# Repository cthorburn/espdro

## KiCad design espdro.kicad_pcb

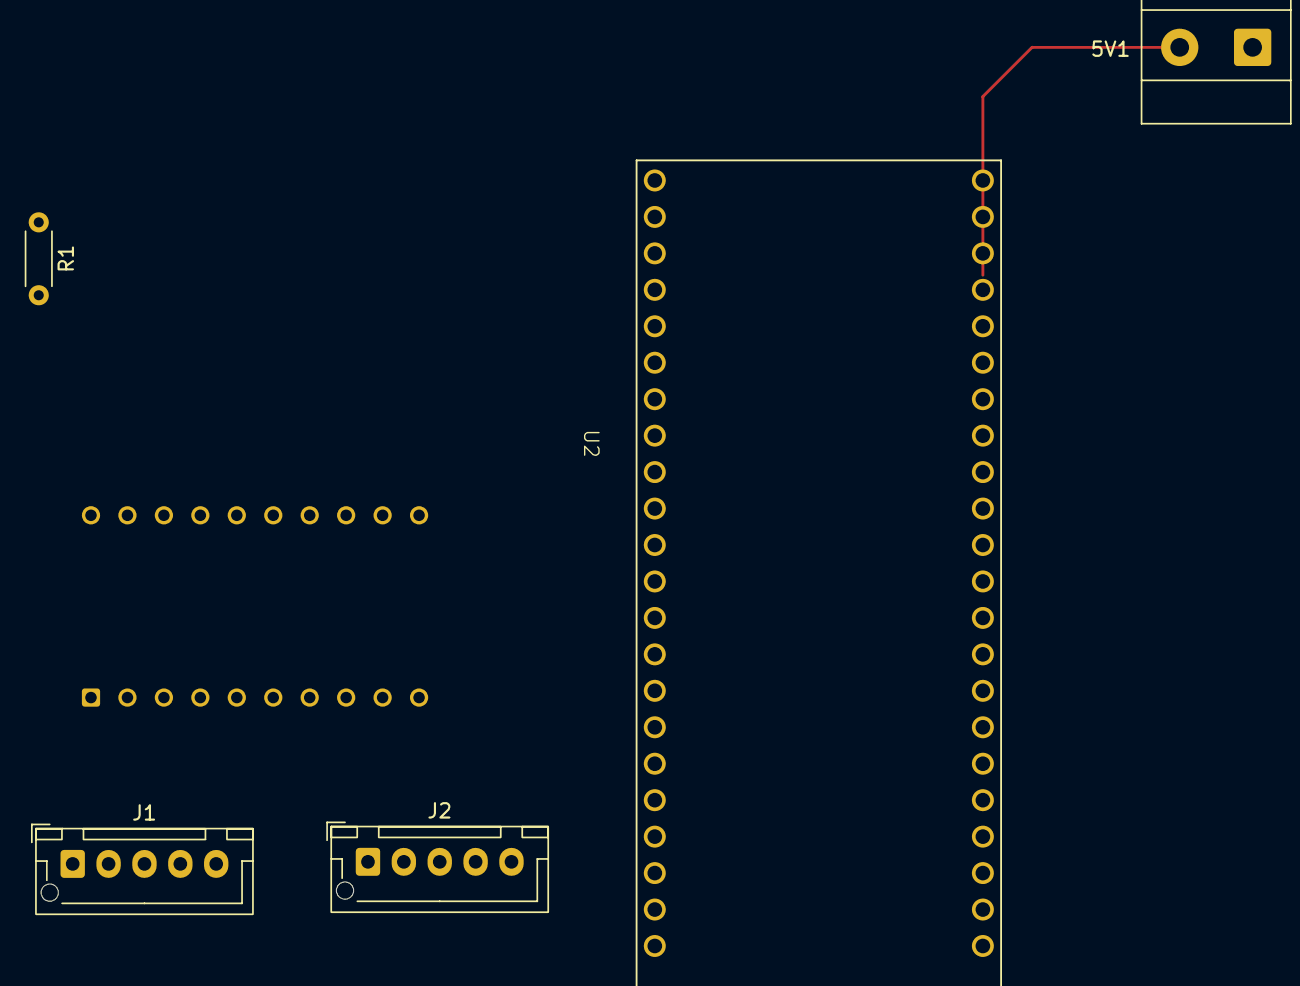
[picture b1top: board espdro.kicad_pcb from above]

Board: 2 copper layers, 6 parts (0 on the bottom side), 16 nets.

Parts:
5V1: GND; TerminalBlock_Phoenix_MKDS-1,5-2-5.08_1x02_P5.08mm_Horizont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
J1: LED&KEY_X; JST_XH_B5B-XH-AM_1x05_P2.50mm_Vertical
J2: LED&KEY_Z; JST_XH_B5B-XH-AM_1x05_P2.50mm_Vertical
R1: 10K; R_Axial_DIN0204_L3.6mm_D1.6mm_P5.08mm_Horizontal
U1: ESP32-S3-DEVKITC-1U-N8R8; MODULE_ESP32-S3-DEVKITC-1U-N8R8
U2: Untitled

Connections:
GND: 5V1.2, J1.2, J2.2, U1.J1_22 (GND), U2.20 (GND)
unnamed: J1.3, U2.12 (B1)
unnamed: J1.4, U2.13 (B2)
unnamed: J1.5, U2.14 (B3)
unnamed: J2.3, U2.15 (B4)
unnamed: J2.4, U2.16 (B5)
unnamed: J2.5, U2.17 (B6)
unnamed: U1.J1_5 (GPIO5), U2.2 (A1)
unnamed: U1.J1_6 (GPIO6), U2.3 (A2)
unnamed: U1.J1_7 (GPIO7), U2.4 (A3)
unnamed: U1.J1_12 (GPIO8), U2.5 (A4)
unnamed: U1.J1_15 (GPIO9), U2.6 (A5)
unnamed: U1.J1_16 (GPIO10), U2.7 (A6)
unnamed: R1.2, U2.10 (OE)
VCC3V3: R1.1, U1.J1_2 (3V3__1), U2.1 (VA)
VCC5V: 5V1.1, J1.1, J2.1, U1.J1_21 (5V0), U2.11 (VB)
